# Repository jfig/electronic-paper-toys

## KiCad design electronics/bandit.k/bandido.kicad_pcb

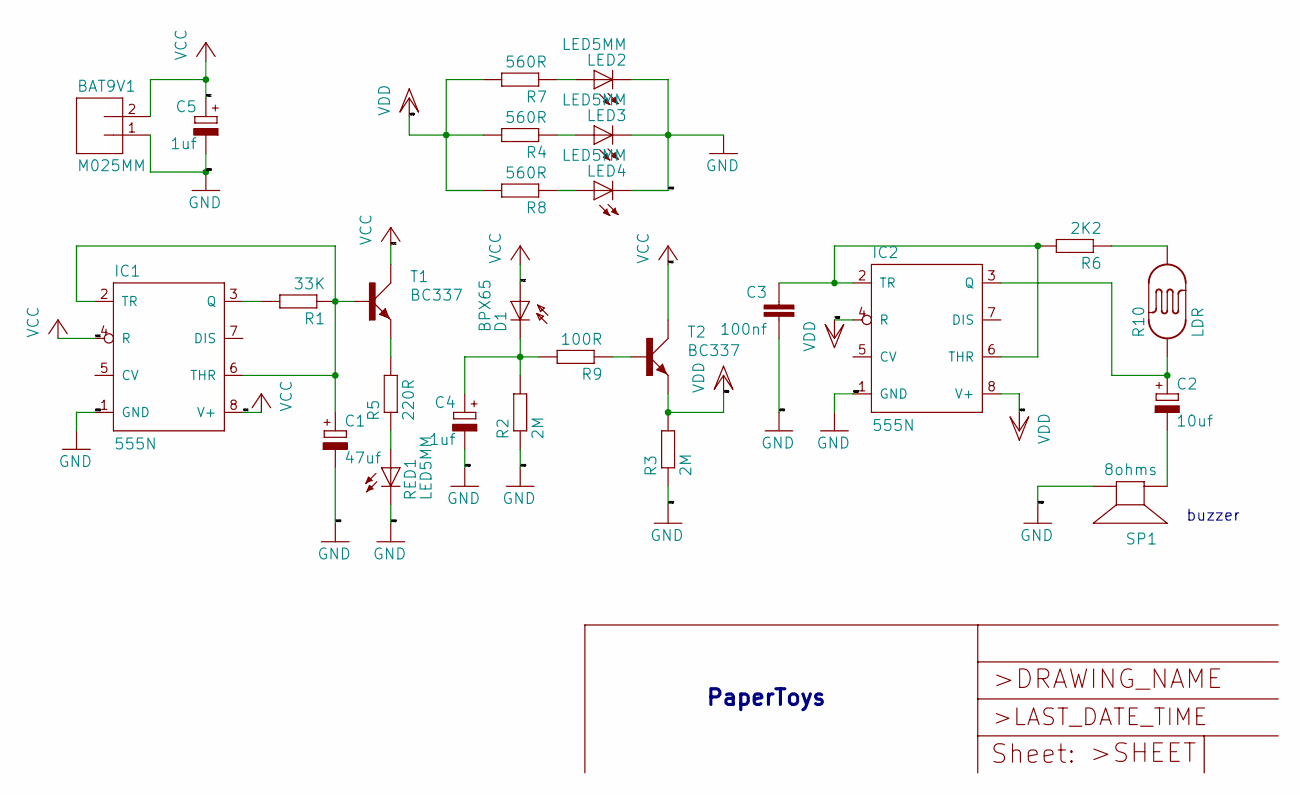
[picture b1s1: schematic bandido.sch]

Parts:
BAT9V1: M025MM; SCREWTERMINAL-5MM-2
C1: 47uf; E5-4
C2: 10uf; E5-4
C3: 100nf; C025-024X044
C4, C5: 1uf; E5-4
D1: BPX65
IC1, IC2: 555N; DIL08-ROUND
LED2, LED3, LED4: LED5MM
R1: 33K; 0204_7
R2, R3: 2M; 0204_7
R4, R7, R8: 560R; 0204_7
R5: 220R; 0204_7
R6: 2K2; 0204_7
R9: 100R; 0204_7
R10: LDR; PHOTOCELL-KIT
RED1: LED5MM
SP1: 8ohms; AL11P
T1, T2: BC337; SOT54A

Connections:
GND: BAT9V1.1, C1.-, C3.2, C4.-, C5.-, IC1.1 (GND), IC2.1 (GND), LED2.K (C), LED3.K (C), LED4.K (C), R2.1, R3.1, RED1.K (C), SP1.-
unnamed: C1.+, IC1.2 (TR), IC1.6 (THR), R1.1, T1.B
unnamed: C2.+, IC2.3 (Q), R10.1
unnamed: C2.-, SP1.+
unnamed: C3.1, IC2.2 (TR), IC2.6 (THR), R6.2
unnamed: C4.+, D1.K (C), R2.2, R9.2
unnamed: IC1.3 (Q), R1.2
unnamed: LED2.A, R7.1
unnamed: LED3.A, R4.1
unnamed: LED4.A, R8.1
unnamed: R5.1, RED1.A
unnamed: R5.2, T1.E
unnamed: R9.1, T2.B
unnamed: R6.1, R10.2
VCC: BAT9V1.2, C5.+, D1.A, IC1.4 (R), IC1.8 (V+), T1.C, T2.C
VDD: IC2.4 (R), IC2.8 (V+), R3.2, R4.2, R7.2, R8.2, T2.E

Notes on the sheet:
PaperToys
buzzer

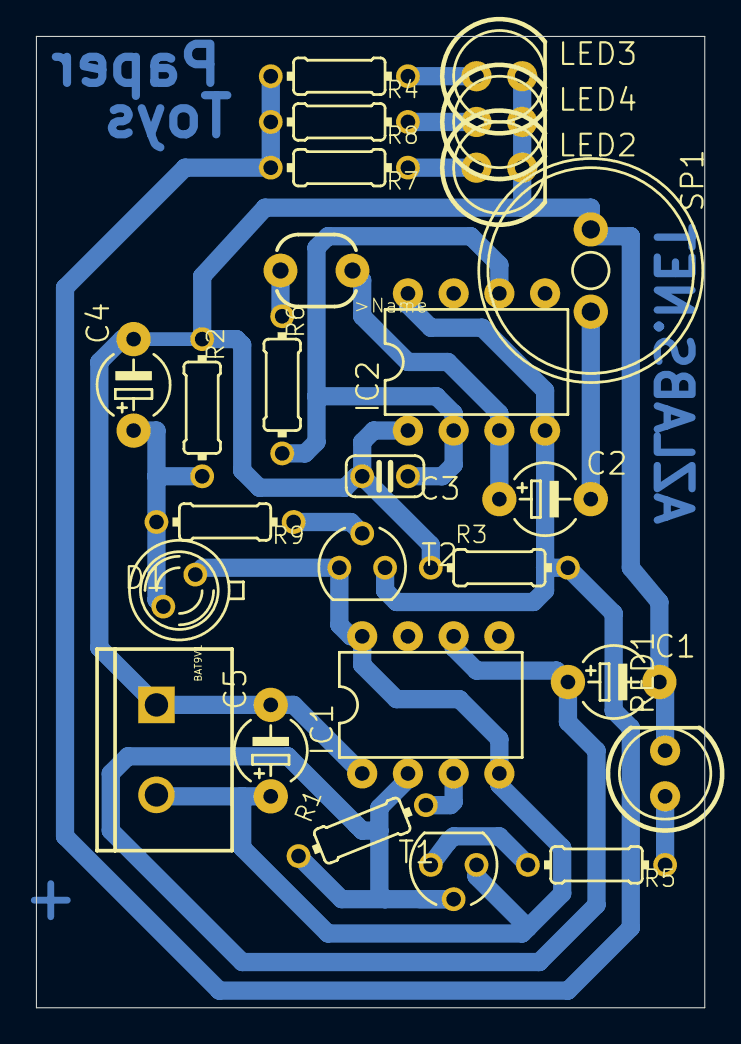
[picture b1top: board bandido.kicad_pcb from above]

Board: 16 copper layers, 37.1 x 54.0 mm, 26 parts (0 on the bottom side), 16 nets.

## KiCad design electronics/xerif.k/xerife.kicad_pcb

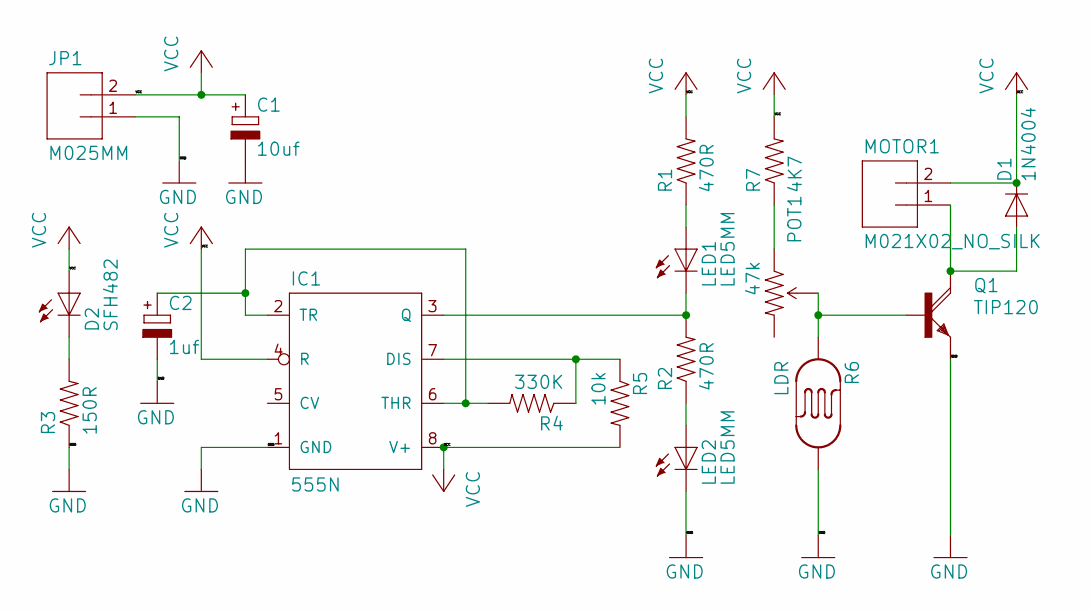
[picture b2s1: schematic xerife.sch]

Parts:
C1: 10uf; E5-5
C2: 1uf; E5-5
D1: 1N4004; DO41-10
D2: SFH482
IC1: 555N; DIL08-ROUND
JP1: M025MM; SCREWTERMINAL-5MM-2
LED1, LED2: LED5MM
MOTOR1: M021X02_NO_SILK; 1X02_NO_SILK
POT1: 47k; TRIM_POT_PTH
Q1: TIP120; TO220AH
R1, R2: 470R; AXIAL-0.4
R3: 150R; AXIAL-0.4
R4: 330K; AXIAL-0.4
R5: 10k; AXIAL-0.4
R6: LDR; PHOTOCELL-KIT
R7: 4K7; AXIAL-0.4

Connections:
GND: C1.-, C2.-, IC1.1 (GND), JP1.1, LED2.K (C), Q1.E, R3.P$1 (1), R6.2
unnamed: C2.+, IC1.2 (TR), IC1.6 (THR), R4.P$2 (2)
unnamed: D1.A, MOTOR1.1, Q1.C
unnamed: D2.K (C), R3.P$2 (2)
unnamed: IC1.3 (Q), LED1.K (C), R2.P$2 (2)
unnamed: IC1.7 (DIS), R4.P$1 (1), R5.P$1 (1)
unnamed: LED1.A, R1.P$1 (1)
unnamed: LED2.A, R2.P$1 (1)
unnamed: POT1.1 (CCW), R7.P$1 (1)
unnamed: POT1.2 (WIPER), Q1.B, R6.1
VCC: C1.+, D1.C, D2.A, IC1.4 (R), IC1.8 (V+), JP1.2, MOTOR1.2, R1.P$2 (2), R5.P$2 (2), R7.P$2 (2)

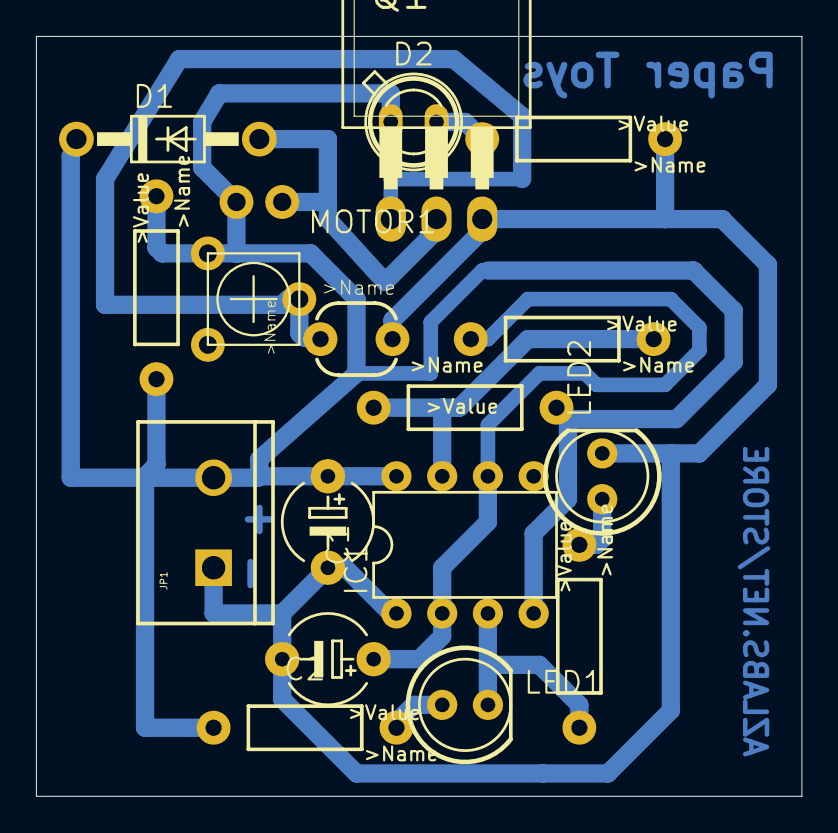
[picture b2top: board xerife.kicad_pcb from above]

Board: 16 copper layers, 42.5 x 42.2 mm, 18 parts (0 on the bottom side), 11 nets.

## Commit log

2021-06-20 convertion to new eagle vertion and import into KiCad
